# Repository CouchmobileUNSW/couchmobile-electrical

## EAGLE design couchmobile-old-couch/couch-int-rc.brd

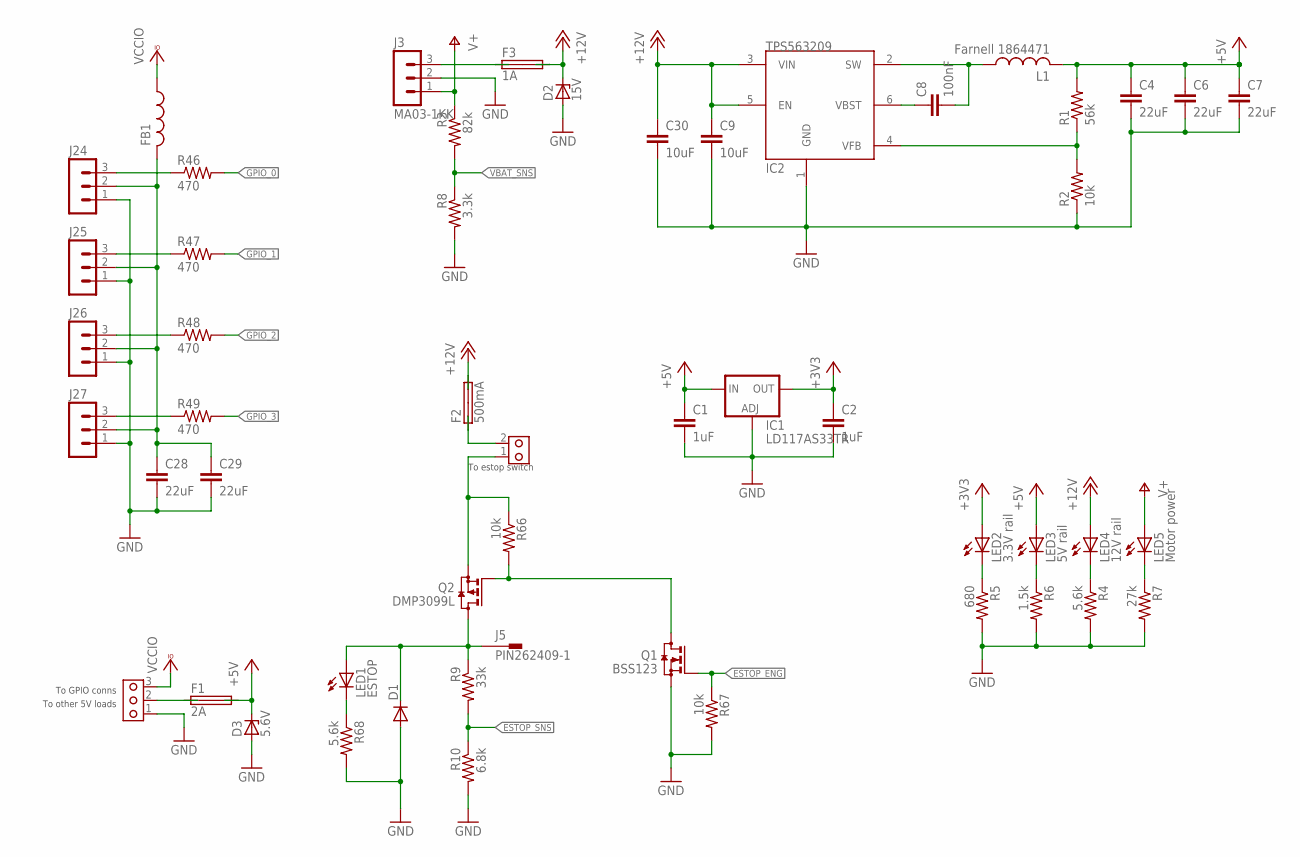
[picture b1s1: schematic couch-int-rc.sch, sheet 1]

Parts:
C1, C2: 1uF; C0603
C4, C6, C7, C28, C29: 22uF; C1206
C8: 100nF; C0603
C9, C30: 10uF; C1206
D1: DIODE-SMB; SMB
D2: 15V; SOD80C
D3: 5.6V; SOD80C
F1: 2A; SHK20L
F2: 500mA; SHK20L
F3: 1A; SHK20L
FB1: L-USL3216C; L3216C
IC1: LD117AS33TR; SOT223
IC2: TPS563209; SOT23-6
J1: PCBTERM3
J3: MA03-1KK; MOLEX-3
J4: PCBTERM2; PCBTERM
J5: PIN262409-1; 62409-1
J24, J25, J26, J27: MA03-1
L1: Farnell 1864471; MCSDRH73B
LED1: ESTOP; CHIPLED_0603
LED2: 3.3V rail; CHIPLED_0603
LED3: 5V rail; CHIPLED_0603
LED4: 12V rail; CHIPLED_0603
LED5: Motor power; CHIPLED_0603
Q1: BSS123; SOT23
Q2: DMP3099L; SOT23
R1: 56k; R0603
R2, R66, R67: 10k; R0603
R3: 82k; R0603
R4, R68: 5.6k; R0603
R5: 680; R0603
R6: 1.5k; R0603
R7: 27k; R0603
R8: 3.3k; R0603
R9: 33k; R0603
R10: 6.8k; R0603
R46, R47, R48, R49: 470; R0603

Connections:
12V_ESTOP: D1.C, J5.A1, J5.A2, LED1.A, Q2.3 (D), R9.1
+3V3: C2.1, IC1.4 (OUT), LED2.A; also elsewhere on the board
+5V: C1.1, C4.1, C6.1, C7.1, D3.C, F1.2A (2), F1.2B (2), IC1.3 (IN), L1.P$2 (2), LED3.A, R1.2; also elsewhere on the board
+12V: C9.1, C30.1, D2.C, F2.2A, F2.2B, F3.2A, F3.2B, IC2.3 (VIN), IC2.5 (EN), LED4.A
ESTOP_ENG: Q1.1 (G), R67.1; also elsewhere on the board
ESTOP_SNS: R9.2, R10.1; also elsewhere on the board
GND: C1.2, C2.2, C4.2, C6.2, C7.2, C9.2, C28.2, C29.2, C30.2, D1.A, D2.A, D3.A, IC1.1 (ADJ), IC2.1 (GND), J1.1, J3.2, J24.1, J25.1, J26.1, J27.1, Q1.2 (S), R2.1, R4.2, R5.2, R6.2, R7.2, R8.2, R10.2, R67.2, R68.2; also elsewhere on the board
GPIO_0: R46.2; also elsewhere on the board
GPIO_1: R47.2; also elsewhere on the board
GPIO_2: R48.2; also elsewhere on the board
GPIO_3: R49.2; also elsewhere on the board
unnamed: IC2.4 (VFB), R1.1, R2.2
unnamed: C8.2, IC2.2 (SW), L1.P$1 (1)
unnamed: F1.1A (1), F1.1B (1), J1.2
unnamed: C8.1, IC2.6 (VBST)
unnamed: LED2.C, R5.1
unnamed: LED3.C, R6.1
unnamed: LED4.C, R4.1
unnamed: LED5.C, R7.1
unnamed: F3.1A, F3.1B, J3.3
unnamed: F2.1A, F2.1B, J4.2
unnamed: Q1.3 (D), Q2.1 (G), R66.2
unnamed: C28.1, C29.1, FB1.2, J24.2, J25.2, J26.2, J27.2
unnamed: J4.1, Q2.2 (S), R66.1
unnamed: LED1.C, R68.1
unnamed: J27.3, R49.1
unnamed: J26.3, R48.1
unnamed: J25.3, R47.1
unnamed: J24.3, R46.1
V+: J3.1, LED5.A, R3.1
VBAT_SNS: R3.2, R8.1; also elsewhere on the board
VCCIO: FB1.1, J1.3

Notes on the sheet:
To other 5V loads
To estop switch
To GPIO conns

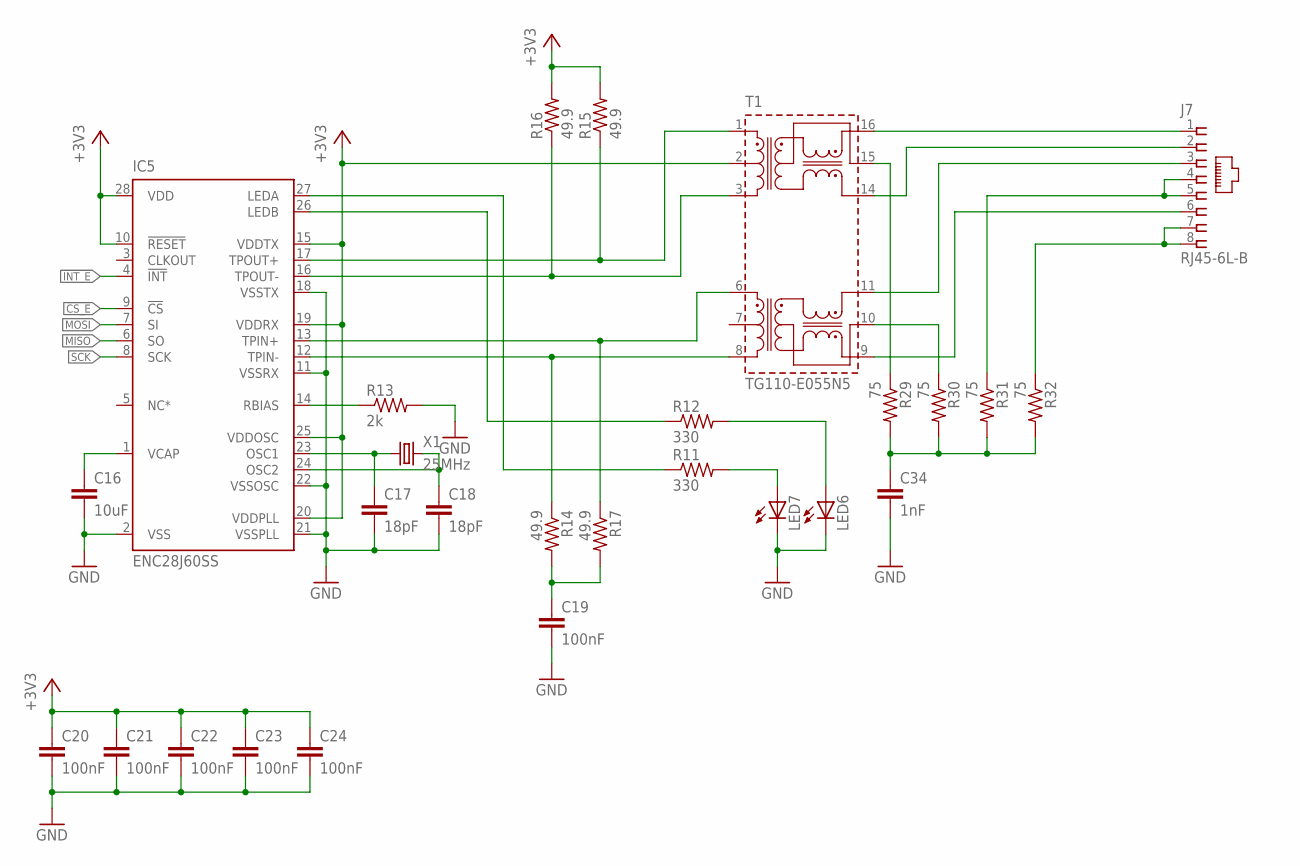
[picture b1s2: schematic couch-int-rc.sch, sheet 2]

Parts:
C16: 10uF; C0603
C17, C18: 18pF; C0603
C19, C20, C21, C22, C23, C24: 100nF; C0603
C34: 1nF; C0603
IC5: ENC28J60SS; SSOP-28
J7: RJ45-6L-B; RJ45-NO-SHIELD
LED6, LED7: LEDCHIP-LED0603; CHIP-LED0603
R11, R12: 330; R0603
R13: 2k; R0603
R14, R15, R16, R17: 49.9; R0603
R29, R30, R31, R32: 75; R0603
T1: TG110-E055N5; N5
X1: 25MHz; HC49/S

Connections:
!CS_E: IC5.9 (!CS); also elsewhere on the board
!INT_E: IC5.4 (!INT); also elsewhere on the board
+3V3: C20.1, C21.1, C22.1, C23.1, C24.1, IC5.10 (!RESET), IC5.15 (VDDTX), IC5.19 (VDDRX), IC5.20 (VDDPLL), IC5.25 (VDDOSC), IC5.28 (VDD), R15.2, R16.2, T1.2; also elsewhere on the board
GND: C16.2, C17.2, C18.2, C19.2, C20.2, C21.2, C22.2, C23.2, C24.2, C34.2, IC5.2 (VSS), IC5.11 (VSSRX), IC5.18 (VSSTX), IC5.21 (VSSPLL), IC5.22 (VSSOSC), LED6.C, LED7.C, R13.2; also elsewhere on the board
MISO: IC5.6 (SO); also elsewhere on the board
MOSI: IC5.7 (SI); also elsewhere on the board
unnamed: LED6.A, R12.2
unnamed: IC5.17 (TPOUT+), R15.1, T1.1
unnamed: IC5.16 (TPOUT-), R16.1, T1.3
unnamed: IC5.13 (TPIN+), R17.1, T1.6
unnamed: IC5.12 (TPIN-), R14.1, T1.8
unnamed: C16.1, IC5.1 (VCAP)
unnamed: IC5.27 (LEDA), R11.1
unnamed: IC5.26 (LEDB), R12.1
unnamed: J7.1, T1.16
unnamed: J7.4, J7.5, R31.1
unnamed: C18.1, IC5.24 (OSC2), X1.2
unnamed: C17.1, IC5.23 (OSC1), X1.1
unnamed: IC5.14 (RBIAS), R13.1
unnamed: LED7.A, R11.2
unnamed: J7.7, J7.8, R32.1
unnamed: C19.1, R14.2, R17.2
unnamed: J7.2, T1.14
unnamed: J7.3, T1.11
unnamed: J7.6, T1.9
unnamed: R29.1, T1.15
unnamed: C34.1, R29.2, R30.2, R31.2, R32.2
unnamed: R30.1, T1.10
SCK: IC5.8 (SCK); also elsewhere on the board

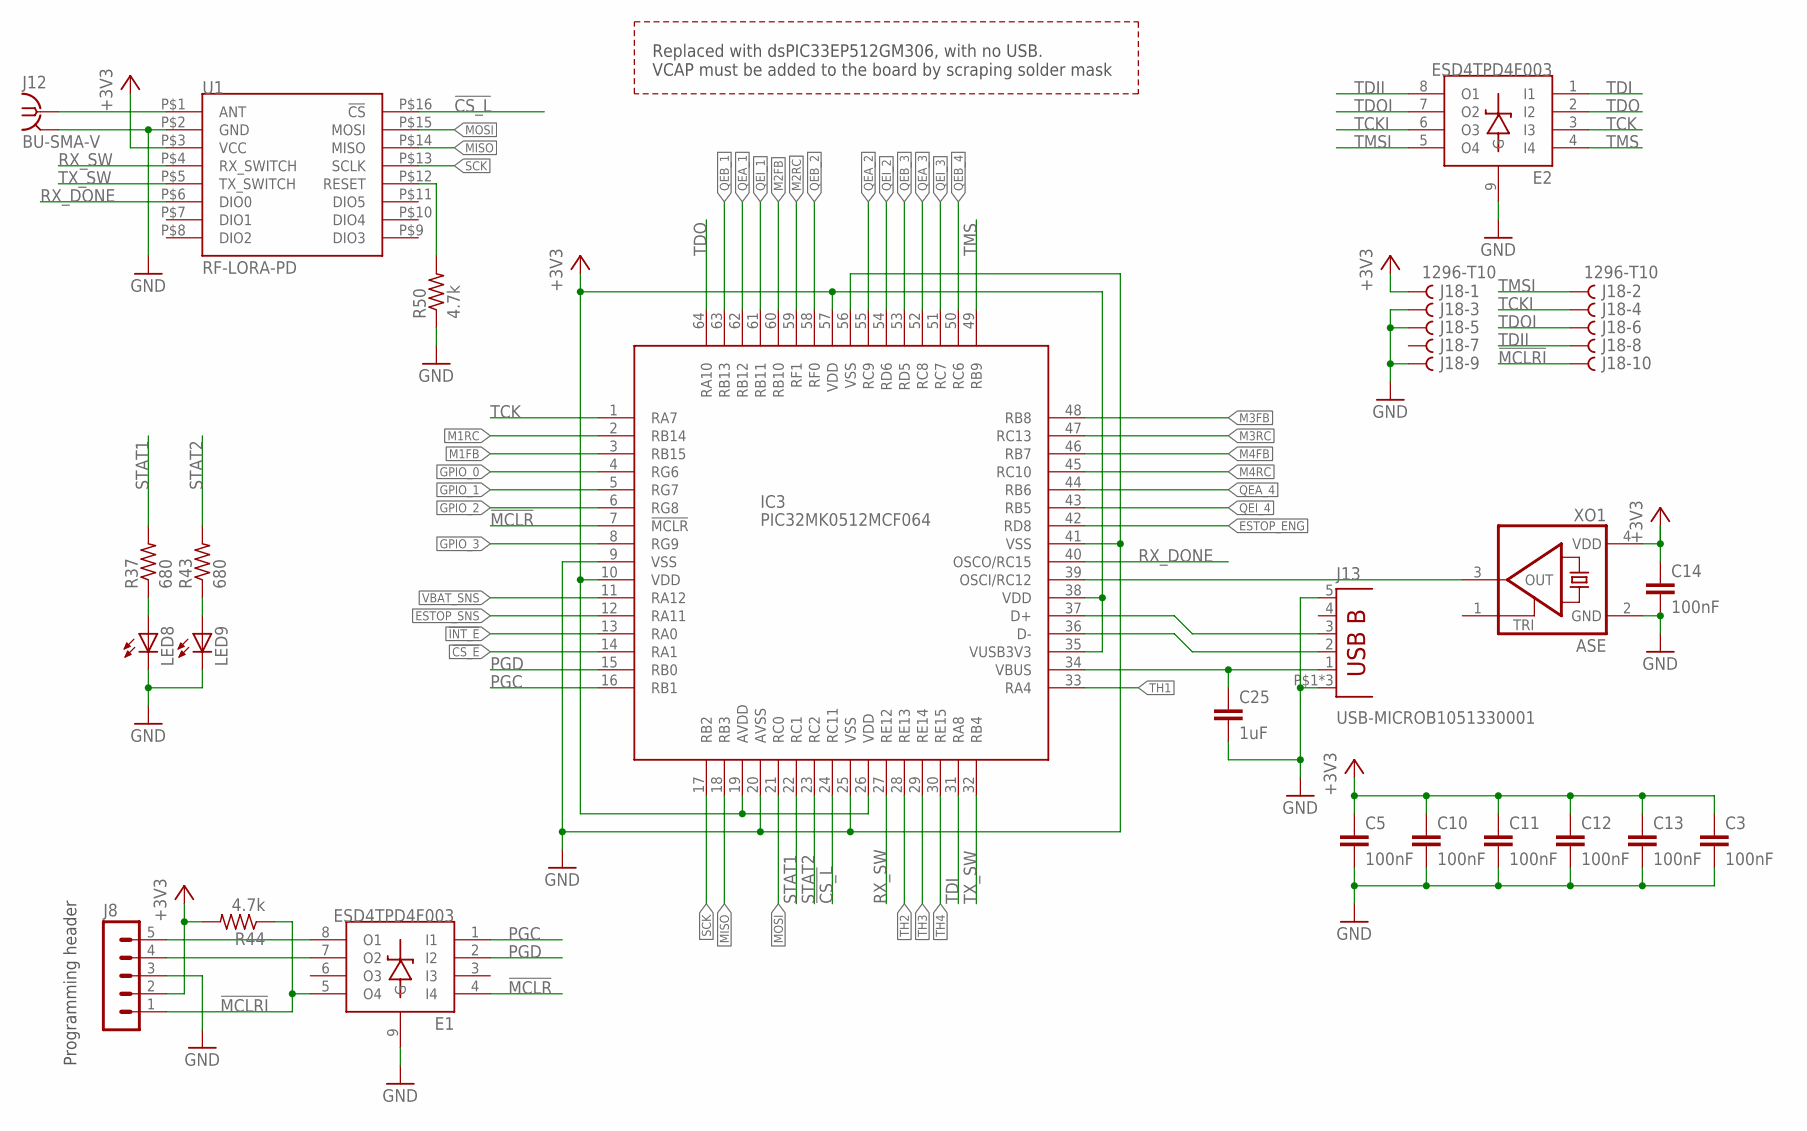
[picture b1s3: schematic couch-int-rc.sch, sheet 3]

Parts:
C3, C5, C10, C11, C12, C13, C14: 100nF; C0603
C25: 1uF; C0603
E1, E2: ESD4TPD4F003; WSON-8
IC3: PIC32MK0512MCF064; TQFP-64-10
J8: MA05-1
J12: BU-SMA-V
J13: USB-MICROB1051330001; 1051330001
J18: 1296-T10; 1296-10
LED8, LED9: LEDCHIP-LED0603; CHIP-LED0603
R37, R43: 680; R0603
R44, R50: 4.7k; R0603
U1: RF-LORA-PD; RF-LORA-DIP
XO1: ASE

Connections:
!CS_E: IC3.14 (RA1); also elsewhere on the board
!CS_L: IC3.24 (RC11), U1.P$16 (!CS)
!INT_E: IC3.13 (RA0); also elsewhere on the board
!MCLR: E1.4 (I4), IC3.7 (!MCLR)
!MCLRI: E1.5 (O4), J8.1, J18.10, R44.1
+3V3: C3.1, C5.1, C10.1, C11.1, C12.1, C13.1, C14.1, IC3.10 (VDD), IC3.19 (AVDD), IC3.26 (VDD), IC3.35 (VUSB3V3), IC3.38 (VDD), IC3.57 (VDD), J8.2, J18.1, R44.2, U1.P$3 (VCC), XO1.4 (VDD); also elsewhere on the board
ESTOP_ENG: IC3.42 (RD8); also elsewhere on the board
ESTOP_SNS: IC3.12 (RA11); also elsewhere on the board
GND: C3.2, C5.2, C10.2, C11.2, C12.2, C13.2, C14.2, C25.2, E1.9 (G), E2.9 (G), IC3.9 (VSS), IC3.20 (AVSS), IC3.25 (VSS), IC3.41 (VSS), IC3.56 (VSS), J8.3, J12.2, J12.3 (2), J12.4 (2), J12.5 (2), J13.5 (GND), J13.P$1 (SHIELD), J13.P$2 (SHIELD), J13.P$3 (SHIELD), J18.3, J18.5, J18.9, LED8.C, LED9.C, R50.1, U1.P$2 (GND), XO1.2 (GND); also elsewhere on the board
GPIO_0: IC3.4 (RG6); also elsewhere on the board
GPIO_1: IC3.5 (RG7); also elsewhere on the board
GPIO_2: IC3.6 (RG8); also elsewhere on the board
GPIO_3: IC3.8 (RG9); also elsewhere on the board
M1FB: IC3.3 (RB15); also elsewhere on the board
M1RC: IC3.2 (RB14); also elsewhere on the board
M2FB: IC3.60 (RB10); also elsewhere on the board
M2RC: IC3.59 (RF1); also elsewhere on the board
M3FB: IC3.48 (RB8); also elsewhere on the board
M3RC: IC3.47 (RC13); also elsewhere on the board
M4FB: IC3.46 (RB7); also elsewhere on the board
M4RC: IC3.45 (RC10); also elsewhere on the board
MISO: IC3.18 (RB3), U1.P$14 (MISO); also elsewhere on the board
MOSI: IC3.21 (RC0), U1.P$15 (MOSI); also elsewhere on the board
unnamed: IC3.39 (OSCI/RC12), XO1.3 (OUT)
unnamed: E1.8 (O1), J8.5
unnamed: E1.7 (O2), J8.4
unnamed: C25.1, IC3.34 (VBUS), J13.1 (VBUS)
unnamed: IC3.36 (D-), J13.2 (D-)
unnamed: IC3.37 (D+), J13.3 (D+)
unnamed: J12.1, U1.P$1 (ANT)
unnamed: R50.2, U1.P$12 (RESET)
unnamed: LED8.A, R37.1
unnamed: LED9.A, R43.1
PGC: E1.1 (I1), IC3.16 (RB1)
PGD: E1.2 (I2), IC3.15 (RB0)
QEA_1: IC3.62 (RB12); also elsewhere on the board
QEA_2: IC3.55 (RC9); also elsewhere on the board
QEA_3: IC3.52 (RC8); also elsewhere on the board
QEA_4: IC3.44 (RB6); also elsewhere on the board
QEB_1: IC3.63 (RB13); also elsewhere on the board
QEB_2: IC3.58 (RF0); also elsewhere on the board
QEB_3: IC3.53 (RD5); also elsewhere on the board
QEB_4: IC3.50 (RC6); also elsewhere on the board
QEI_1: IC3.61 (RB11); also elsewhere on the board
QEI_2: IC3.54 (RD6); also elsewhere on the board
QEI_3: IC3.51 (RC7); also elsewhere on the board
QEI_4: IC3.43 (RB5); also elsewhere on the board
RX_DONE: IC3.40 (OSCO/RC15), U1.P$6 (DIO0)
RX_SW: IC3.27 (RE12), U1.P$4 (RX_SWITCH)
SCK: IC3.17 (RB2), U1.P$13 (SCLK); also elsewhere on the board
STAT1: IC3.22 (RC1), R37.2
STAT2: IC3.23 (RC2), R43.2
TCK: E2.3 (I3), IC3.1 (RA7)
TCKI: E2.6 (O3), J18.4
TDI: E2.1 (I1), IC3.31 (RA8)
TDII: E2.8 (O1), J18.8
TDO: E2.2 (I2), IC3.64 (RA10)
TDOI: E2.7 (O2), J18.6
TH1: IC3.33 (RA4); also elsewhere on the board
TH2: IC3.28 (RE13); also elsewhere on the board
TH3: IC3.29 (RE14); also elsewhere on the board
TH4: IC3.30 (RE15); also elsewhere on the board
TMS: E2.4 (I4), IC3.49 (RB9)
TMSI: E2.5 (O4), J18.2
TX_SW: IC3.32 (RB4), U1.P$5 (TX_SWITCH)
VBAT_SNS: IC3.11 (RA12); also elsewhere on the board

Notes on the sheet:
Programming header
Replaced with dsPIC33EP512GM306, with no USB. VCAP must be added to the board by scraping solder mask

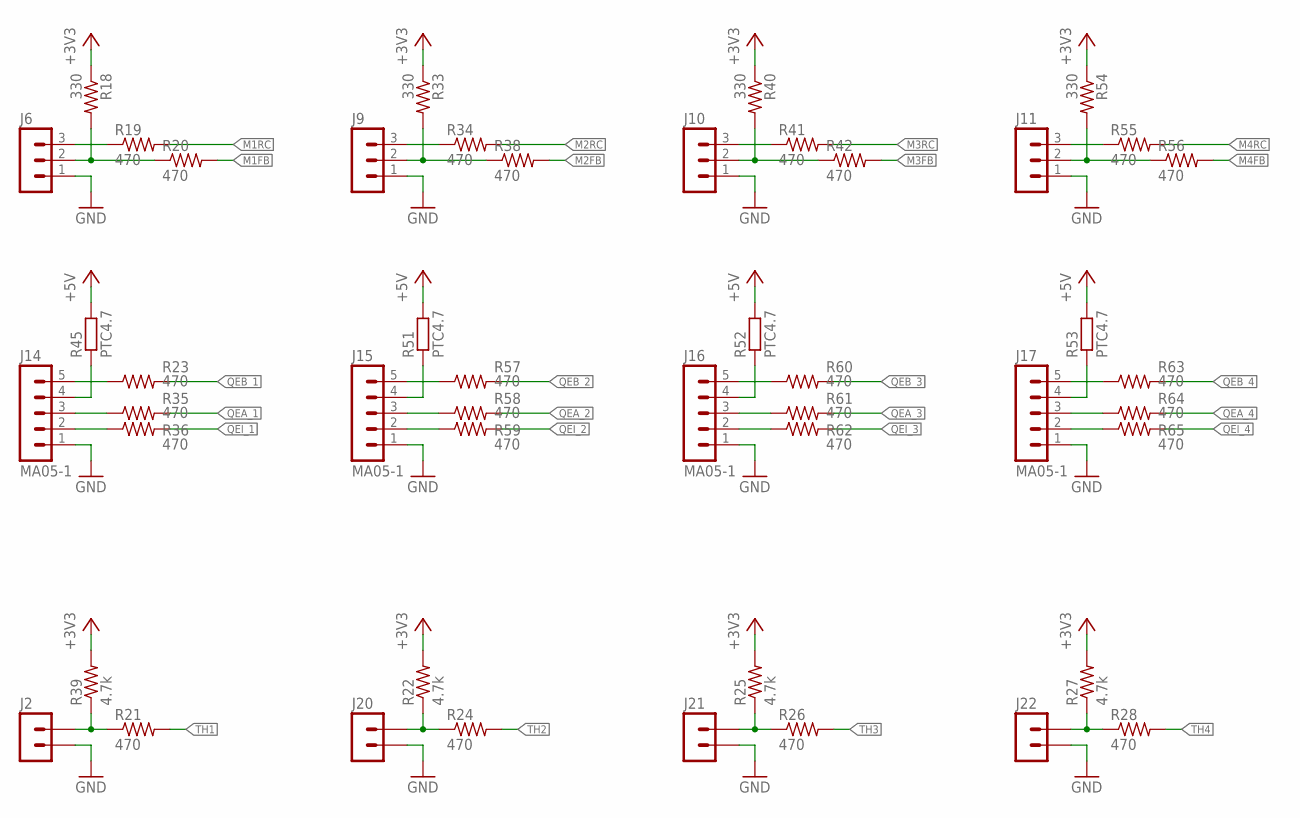
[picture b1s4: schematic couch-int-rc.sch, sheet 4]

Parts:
J2, J20, J21, J22: MA02-1; MOLEX-2
J6, J9, J10, J11: MA03-1
J14, J15, J16, J17: MA05-1; MOLEX-5
R18, R33, R40, R54: 330; R0603
R19, R20, R21, R23, R24, R26, R28, R34, R35, R36, R38, R41, R42, R55, R56, R57, R58, R59, R60, R61, R62, R63, R64, R65: 470; R0603
R22, R25, R27, R39: 4.7k; R0603
R45, R51, R52, R53: PTC4.7; R0603

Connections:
+3V3: R18.1, R22.2, R25.2, R27.2, R33.1, R39.2, R40.1, R54.1; also elsewhere on the board
+5V: R45.2, R51.2, R52.2, R53.2; also elsewhere on the board
GND: J2.1, J6.1, J9.1, J10.1, J11.1, J14.1, J15.1, J16.1, J17.1, J20.1, J21.1, J22.1; also elsewhere on the board
M1FB: R20.2; also elsewhere on the board
M1RC: R19.2; also elsewhere on the board
M2FB: R38.2; also elsewhere on the board
M2RC: R34.2; also elsewhere on the board
M3FB: R42.2; also elsewhere on the board
M3RC: R41.2; also elsewhere on the board
M4FB: R56.2; also elsewhere on the board
M4RC: R55.2; also elsewhere on the board
unnamed: J6.2, R18.2, R20.1
unnamed: J6.3, R19.1
unnamed: J20.2, R22.1, R24.1
unnamed: J2.2, R21.1, R39.1
unnamed: J21.2, R25.1, R26.1
unnamed: J22.2, R27.1, R28.1
unnamed: J9.2, R33.2, R38.1
unnamed: J9.3, R34.1
unnamed: J10.2, R40.2, R42.1
unnamed: J10.3, R41.1
unnamed: J11.2, R54.2, R56.1
unnamed: J11.3, R55.1
unnamed: J14.5, R23.1
unnamed: J14.3, R35.1
unnamed: J14.2, R36.1
unnamed: J15.5, R57.1
unnamed: J15.3, R58.1
unnamed: J15.2, R59.1
unnamed: J16.5, R60.1
unnamed: J16.3, R61.1
unnamed: J16.2, R62.1
unnamed: J17.5, R63.1
unnamed: J17.3, R64.1
unnamed: J17.2, R65.1
unnamed: J15.4, R51.1
unnamed: J14.4, R45.1
unnamed: J16.4, R52.1
unnamed: J17.4, R53.1
QEA_1: R35.2; also elsewhere on the board
QEA_2: R58.2; also elsewhere on the board
QEA_3: R61.2; also elsewhere on the board
QEA_4: R64.2; also elsewhere on the board
QEB_1: R23.2; also elsewhere on the board
QEB_2: R57.2; also elsewhere on the board
QEB_3: R60.2; also elsewhere on the board
QEB_4: R63.2; also elsewhere on the board
QEI_1: R36.2; also elsewhere on the board
QEI_2: R59.2; also elsewhere on the board
QEI_3: R62.2; also elsewhere on the board
QEI_4: R65.2; also elsewhere on the board
TH1: R21.2; also elsewhere on the board
TH2: R24.2; also elsewhere on the board
TH3: R26.2; also elsewhere on the board
TH4: R28.2; also elsewhere on the board

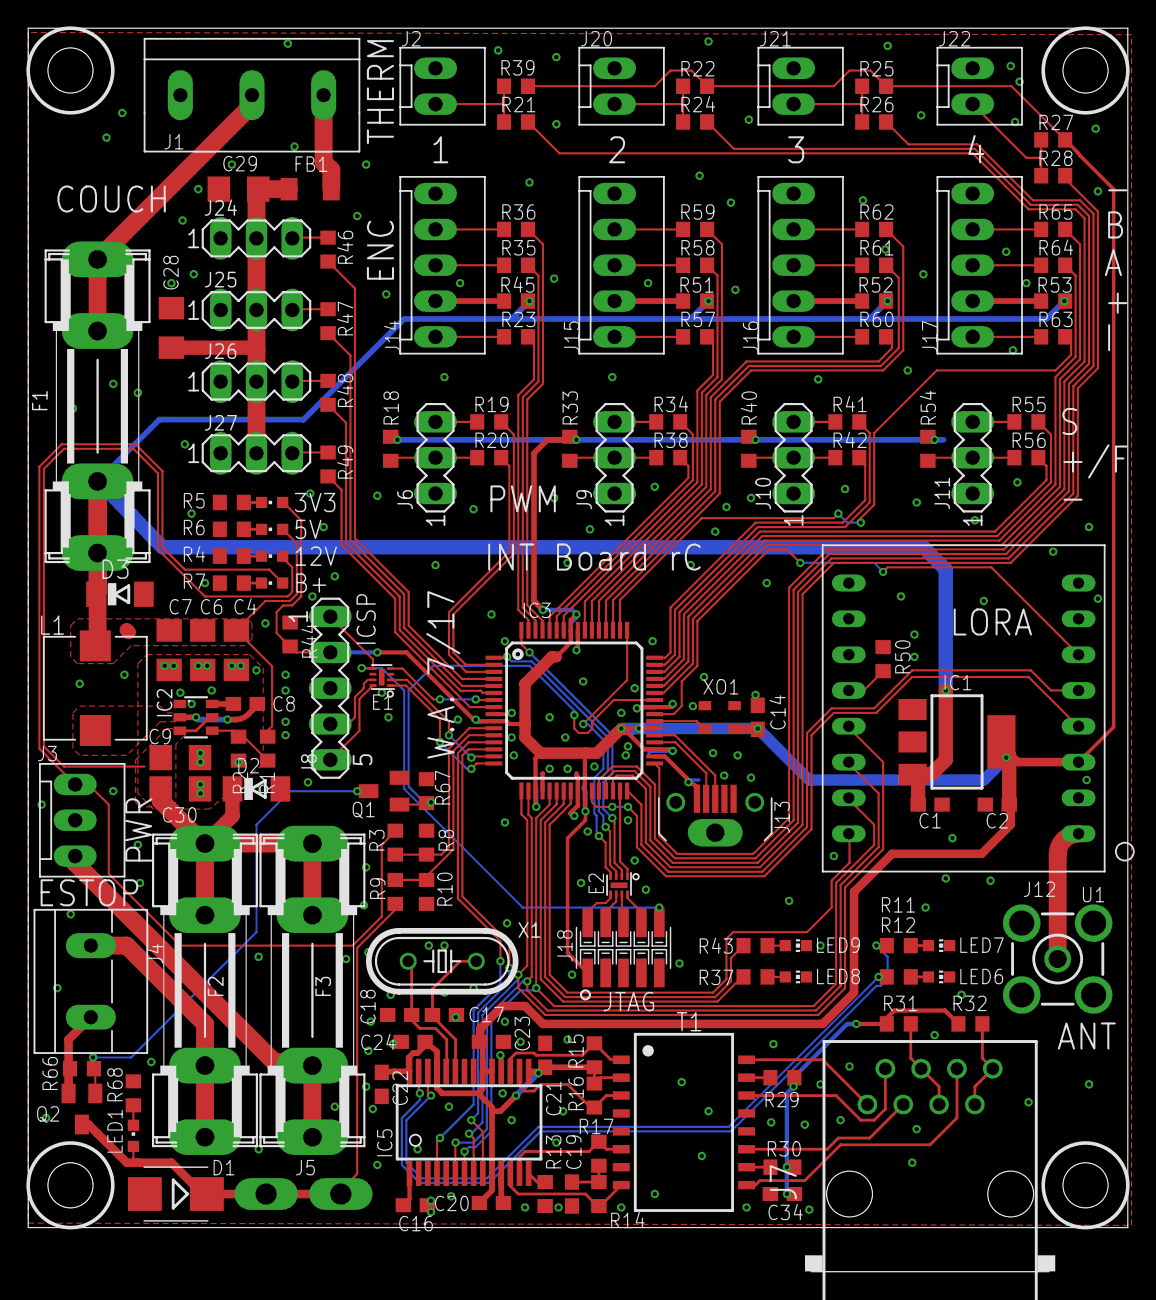
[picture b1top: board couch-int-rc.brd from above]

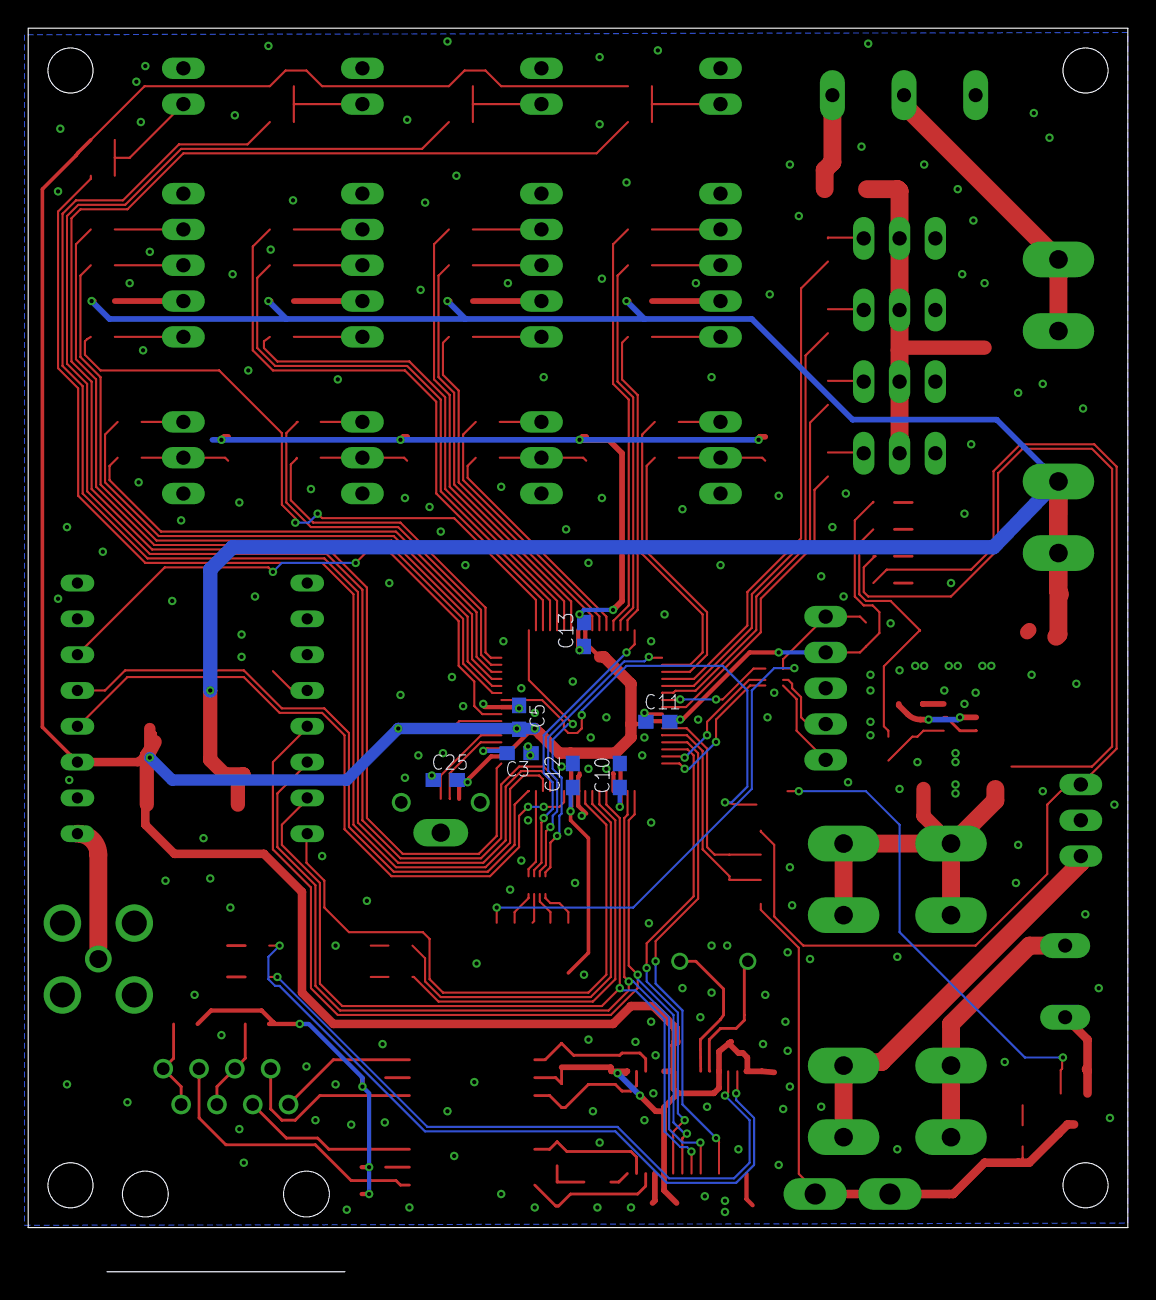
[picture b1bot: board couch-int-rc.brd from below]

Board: 2 copper layers, 78.0 x 88.2 mm, 150 parts (7 on the bottom side), 139 nets.

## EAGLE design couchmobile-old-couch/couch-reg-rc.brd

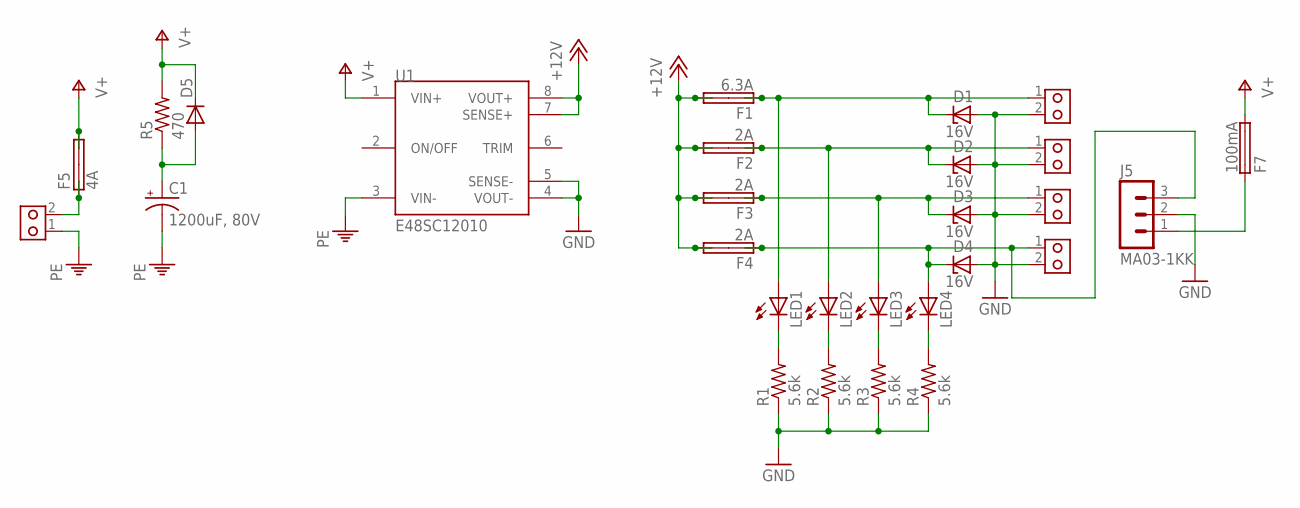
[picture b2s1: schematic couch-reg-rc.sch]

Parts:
C1: 1200uF, 80V; E7,5-18
D1, D2, D3, D4: 16V; C1702-15
D5: DIODE-SMB; SMB
F1: 6.3A; SHK20L
F2, F3, F4: 2A; SHK20L
F5: 4A; SHK20L
F7: 100mA; 0603
J1, J2, J3, J4, J6: PCBTERM2; PCBTERM
J5: MA03-1KK; MOLEX-3
LED1, LED2, LED3, LED4: LEDCHIPLED_0603; CHIPLED_0603
R1, R2, R3, R4: 5.6k; R0603
R5: 470; R0603
U1: E48SC12010

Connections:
+12V: F1.2A, F1.2B, F2.2A, F2.2B, F3.2A, F3.2B, F4.2A, F4.2B, U1.7 (SENSE+), U1.8 (VOUT+)
GND: D1.A, D2.A, D3.A, D4.A, J1.2, J2.2, J3.2, J4.2, J5.2, R1.1, R2.1, R3.1, R4.1, U1.4 (VOUT-), U1.5 (SENSE-)
unnamed: C1.+, D5.A, R5.1
unnamed: D4.C, F4.1A, F4.1B, J4.1, J5.3, LED4.A
unnamed: D1.C, F1.1A, F1.1B, J1.1, LED1.A
unnamed: D2.C, F2.1A, F2.1B, J2.1, LED2.A
unnamed: D3.C, F3.1A, F3.1B, J3.1, LED3.A
unnamed: F7.1, J5.1
unnamed: LED1.C, R1.2
unnamed: LED2.C, R2.2
unnamed: LED3.C, R3.2
unnamed: LED4.C, R4.2
unnamed: F5.1A, F5.1B, J6.2
PE: C1.-, J6.1, U1.3 (VIN-)
V+: D5.C, F5.2A, F5.2B, F7.2, R5.2, U1.1 (VIN+)

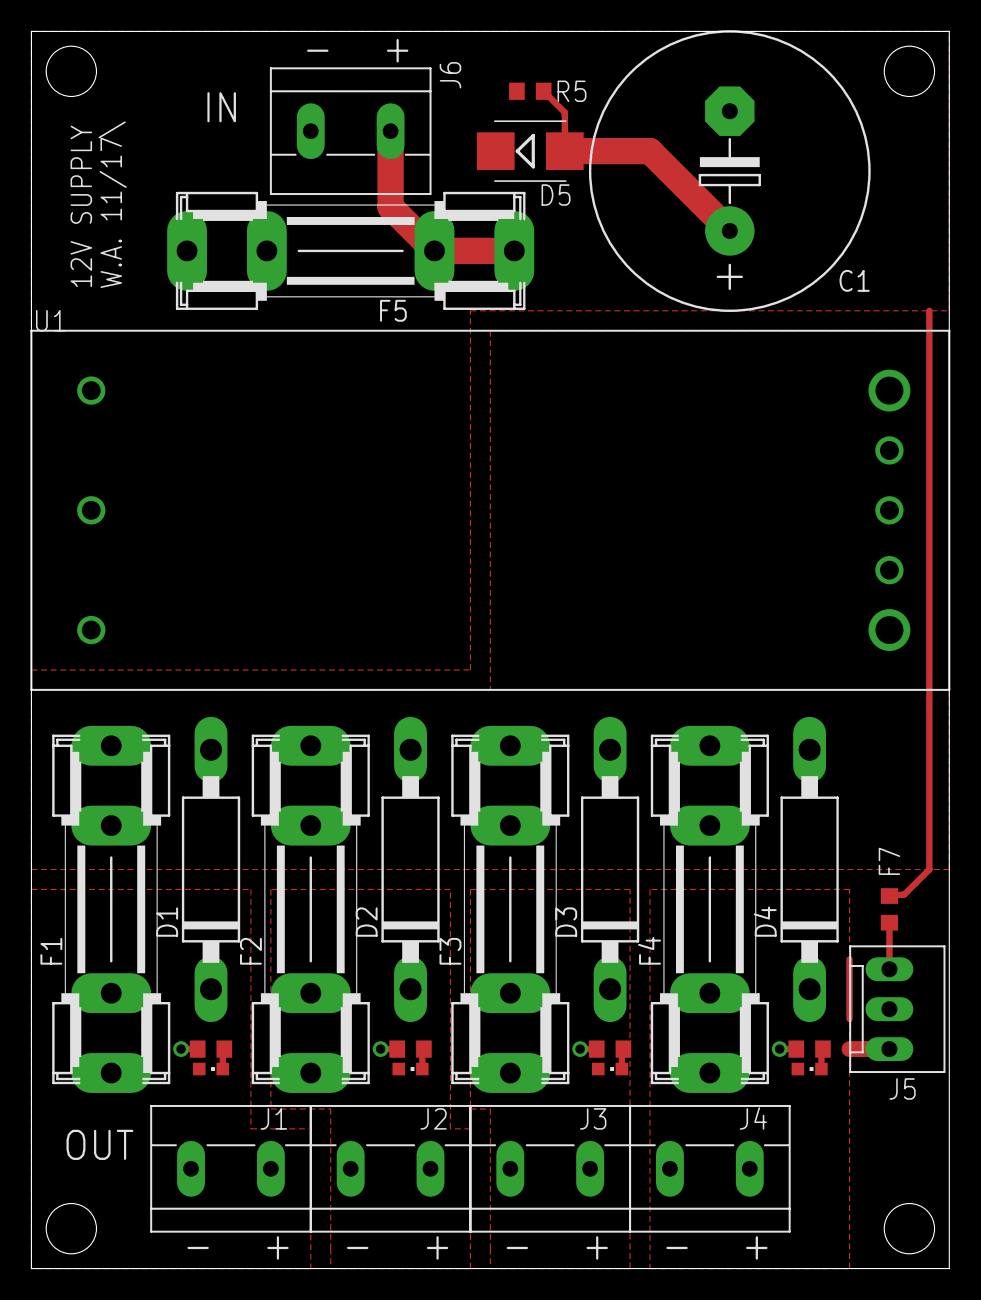
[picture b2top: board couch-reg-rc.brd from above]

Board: 2 copper layers, 58.4 x 78.7 mm, 28 parts (0 on the bottom side), 15 nets.

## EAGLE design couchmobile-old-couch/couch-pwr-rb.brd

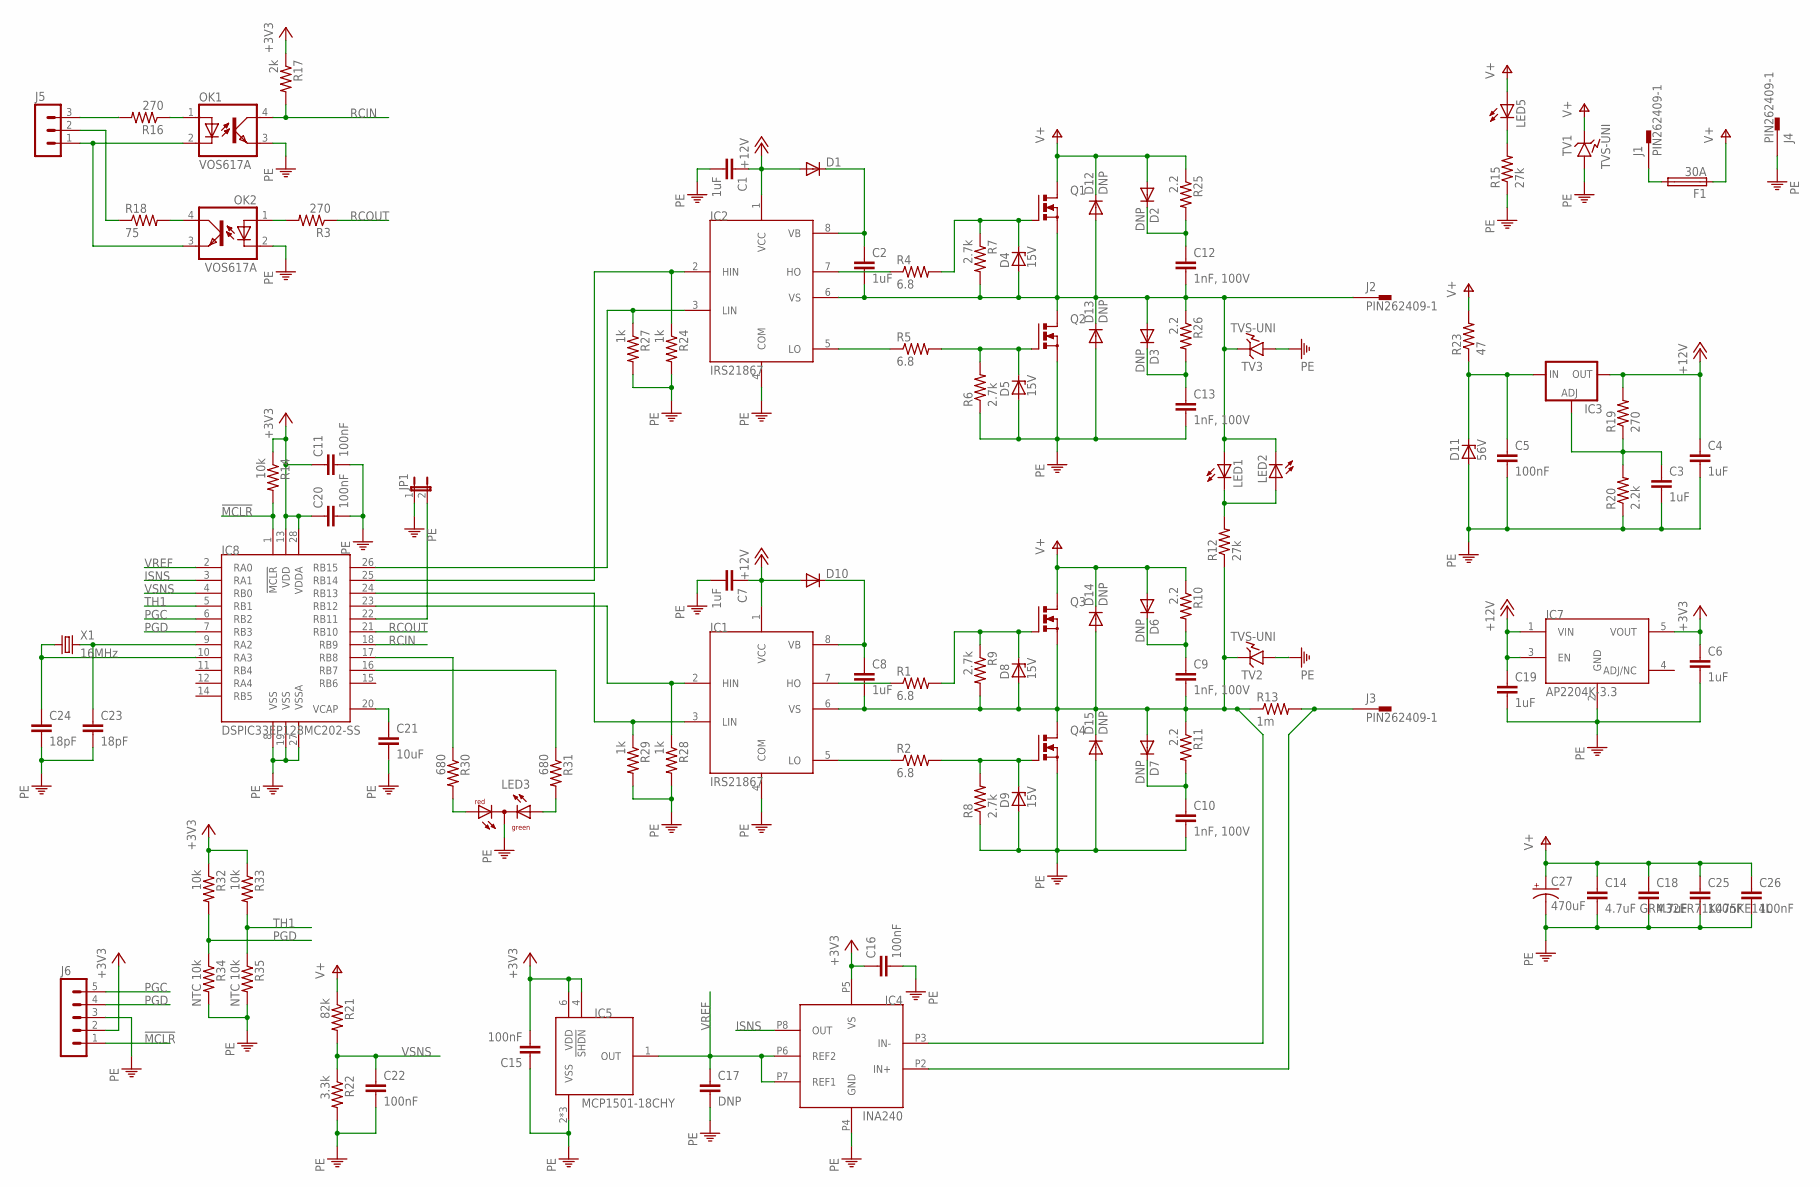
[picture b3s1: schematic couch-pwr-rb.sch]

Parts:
C1, C2, C3, C4, C7, C8: 1uF; C0805
C5: 100nF; C0805
C6, C19: 1uF; C0603
C9, C10, C12, C13: 1nF, 100V; C1206
C11, C15, C16, C20, C22: 100nF; C0603
C14: 4.7uF GRM32ER71K475KE14L; C1210
C17: DNP; C0603
C18: 4.7uF; C1210
C21: 10uF; C0603
C23, C24: 18pF; C0603
C25, C26: 100nF; C1206
C27: 470uF; E7,5-16
D1, D10: DIODE-SOD323-W; SOD323-W
D2, D3, D6, D7: DNP; DO-214AC
D4, D5, D8, D9: 15V; SOD80C
D11: 56V; SMB
D12, D13, D14, D15: DNP; SMC
F1: 30A; BLADEFUSE
IC1, IC2: IRS21867; SO-08
IC3: LM317TLBH; TO220BH
IC4: INA240; VSSOP-8
IC5: MCP1501-18CHY; SOT23-6
IC7: AP2204K-3.3; SOT23-5
IC8: DSPIC33EP128MC202-SS; SSOP-28
J1, J2, J3, J4: PIN262409-1; 62409-1
J5: MA03-1
J6: MA05-1
JP1: JP1E; JP1
LED1, LED2, LED5: LEDCHIP-LED0603; CHIP-LED0603
LED3: DUOLED-RG-C; DUOLED-C-5MM
OK1, OK2: VOS617A; MINI-FLAT-4
Q1, Q2, Q3, Q4: PMOSFET_NTO220BH; TO220BH
R1, R2, R4, R5: 6.8; R1206
R3, R16, R19: 270; R0603
R6, R7, R8, R9: 2.7k; R0603
R10, R11, R25, R26: 2.2; R1206
R12, R15: 27k; R0603
R13: 1m; R2512
R14, R32, R33: 10k; R0603
R17: 2k; R0603
R18: 75; R0603
R20: 2.2k; R0603
R21: 82k; R0603
R22: 3.3k; R0603
R23: 47; R1206
R24, R27, R28, R29: 1k; R0603
R30, R31: 680; R0603
R34, R35: NTC 10k; R0603
TV1, TV2, TV3: TVS-UNI; SMC
X1: 16MHz; HC49/S

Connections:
!MCLR: IC8.1 (!MCLR), J6.1, R14.2
+3V3: C6.1, C11.1, C15.2, C16.1, C20.1, IC4.P5 (VS), IC5.4 (!SHDN), IC5.6 (VDD), IC7.5 (VOUT), IC8.13 (VDD), IC8.28 (VDDA), J6.2, R14.1, R17.1, R32.1, R33.1
+12V: C1.1, C4.1, C7.1, C19.1, D1.A, D10.A, IC1.1 (VCC), IC2.1 (VCC), IC3.D (OUT), IC7.1 (VIN), IC7.3 (EN), R19.2
ISNS: IC4.P8 (OUT), IC8.3 (RA1)
MD1: C2.2, C12.2, D3.A, D4.A, D12.A, D13.C, IC2.6 (VS), J2.A1, J2.A2, LED1.A, LED2.C, Q1.S, Q2.D, R7.2, R26.1, TV3.1 (M1)
MD2: C8.2, C9.2, D7.A, D8.A, D14.A, D15.C, IC1.6 (VS), IC4.P3 (IN-), Q3.S, Q4.D, R9.2, R11.1, R12.1, R13.1, TV2.1 (M1)
unnamed: D5.C, Q2.G, R5.2, R6.2
unnamed: F1.2A (2), F1.2B (2), J1.A1, J1.A2
unnamed: D4.C, Q1.G, R4.2, R7.1
unnamed: IC2.7 (HO), R4.1
unnamed: C2.1, D1.C, IC2.8 (VB)
unnamed: IC2.5 (LO), R5.1
unnamed: C13.1, D3.C, R26.2
unnamed: D9.C, Q4.G, R2.2, R8.2
unnamed: D8.C, Q3.G, R1.2, R9.1
unnamed: IC1.7 (HO), R1.1
unnamed: C8.1, D10.C, IC1.8 (VB)
unnamed: IC1.5 (LO), R2.1
unnamed: C9.1, D6.C, R10.2
unnamed: C10.1, D7.C, R11.2
unnamed: C5.1, D11.C, IC3.S (IN), R23.1
unnamed: LED1.C, LED2.A, R12.2
unnamed: C21.1, IC8.20 (VCAP)
unnamed: IC1.2 (HIN), IC8.23 (RB12), R28.1
unnamed: C23.1, IC8.9 (RA2), X1.2
unnamed: IC2.2 (HIN), IC8.25 (RB14), R24.1
unnamed: LED5.C, R15.2
unnamed: C24.1, IC8.10 (RA3), X1.1
unnamed: OK2.1 (A), R3.2
unnamed: C12.1, D2.C, R25.2
unnamed: OK2.4 (COL), R18.2
unnamed: IC2.3 (LIN), IC8.26 (RB15), R27.1
unnamed: IC1.3 (LIN), IC8.24 (RB13), R29.1
unnamed: J5.1, OK1.2 (C), OK2.3 (EMIT)
unnamed: J5.2, R18.1
unnamed: IC4.P2 (IN+), J3.A1, J3.A2, R13.2
unnamed: J5.3, R16.2
unnamed: OK1.1 (A), R16.1
unnamed: C3.1, IC3.G (ADJ), R19.1, R20.2
unnamed: IC8.17 (RB8), R30.1
unnamed: IC8.16 (RB7), R31.1
unnamed: IC8.22 (RB11), JP1.2
unnamed: LED3.AR, R30.2
unnamed: LED3.AX (AG), R31.2
PE: C1.2, C3.2, C4.2, C5.2, C6.2, C7.2, C10.2, C11.2, C13.2, C14.2, C15.1, C16.2, C17.2, C18.2, C19.2, C20.2, C21.2, C22.2, C23.2, C24.2, C25.2, C26.2, C27.-, D5.A, D9.A, D11.A, D13.A, D15.A, IC1.4 (COM), IC2.4 (COM), IC4.P4 (GND), IC5.2 (VSS), IC5.3 (VSS), IC5.5 (VSS), IC7.2 (GND), IC8.8 (VSS), IC8.19 (VSS), IC8.27 (VSSA), J4.A1, J4.A2, J6.3, JP1.1, LED3.C, OK1.3 (EMIT), OK2.2 (C), Q2.S, Q4.S, R6.1, R8.1, R15.1, R20.1, R22.2, R24.2, R27.2, R28.2, R29.2, R34.2, R35.2, TV1.2 (M2), TV2.2 (M2), TV3.2 (M2)
PGC: IC8.6 (RB2), J6.5
PGD: IC8.7 (RB3), J6.4, R32.2, R34.1
RCIN: IC8.18 (RB9), OK1.4 (COL), R17.2
RCOUT: IC8.21 (RB10), R3.1
TH1: IC8.5 (RB1), R33.2, R35.1
V+: C14.1, C18.1, C25.1, C26.1, C27.+, D2.A, D6.A, D12.C, D14.C, F1.1A (1), F1.1B (1), LED5.A, Q1.D, Q3.D, R10.1, R21.1, R23.2, R25.1, TV1.1 (M1)
VREF: C17.1, IC4.P6 (REF2), IC4.P7 (REF1), IC5.1 (OUT), IC8.2 (RA0)
VSNS: C22.1, IC8.4 (RB0), R21.2, R22.1
